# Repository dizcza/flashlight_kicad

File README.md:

# Flashlight PCB design with wooden casing

Kicad PCB design for my wooden flashlight V1 (see https://github.com/dizcza/lasercut_collection). Originally designed by HackLabKyiv residents.

An ordinary 12V LED strip is soldered to the front side of the PCB.

<table>
  <tr>
   <td></td>
   <td></td>
  </tr>
</table>

## Schematics

[schematics.pdf](schematics.pdf)

## Revisions

<table>
  <tr>
   <th>V1</th>
   <th>V2.1</th>
   <th>V2.2</th>
   <th>V3.0</th>
  </tr>
  <tr>
   <td></td>
   <td></td>
   <td></td>
   <td></td>
  </tr>
</table>

## BOM

|Comment             |Designator|Footprint                      |LCSC    |
|--------------------|----------|-------------------------------|--------|
|22uF/25V            |C1,C3,C4  |Capacitor_SMD:C_0805_2012Metric|C45783  |
|1uF                 |C2        |Capacitor_SMD:C_0603_1608Metric|C15849  |
|D_Schottky          |D1,D4,D5  |Diode_SMD:D_SMB                |C22452  |
|USB_B_Micro         |J1        |FlashlightLib:USB-1101IPX6-02  |C2858269|
|10uH                |L1        |FlashlightLib:L_5.0x5.0        |C2849501|
|HSS2333             |Q2        |Package_TO_SOT_SMD:SOT-23      |C15127  |
|1k                  |R1,R2,R3  |Resistor_SMD:R_0603_1608Metric |C21190  |
|10k                 |R4,R6     |Resistor_SMD:R_0603_1608Metric |C25804  |
|200k                |R7        |Resistor_SMD:R_0603_1608Metric |C25811  |
|XB4908A             |U1        |FlashlightLib:XB4908A          |C2998740|
|MT3608              |U2        |Package_TO_SOT_SMD:SOT-23-6    |C84817  |
|TP4057              |U3        |Package_TO_SOT_SMD:TSOT-23-6   |C12044  |
|R6BHC-A05_LED-19-223|U4        |MyFootprints:R6BHC-A05_LED     |C131286 |

## Casing

Can be lasercut or 3d-printed.

DXF file: [casing.dxf](./casing/casing.dxf)

OpenSCAD design file: https://github.com/dizcza/lasercut_collection/blob/master/Lampa.scad

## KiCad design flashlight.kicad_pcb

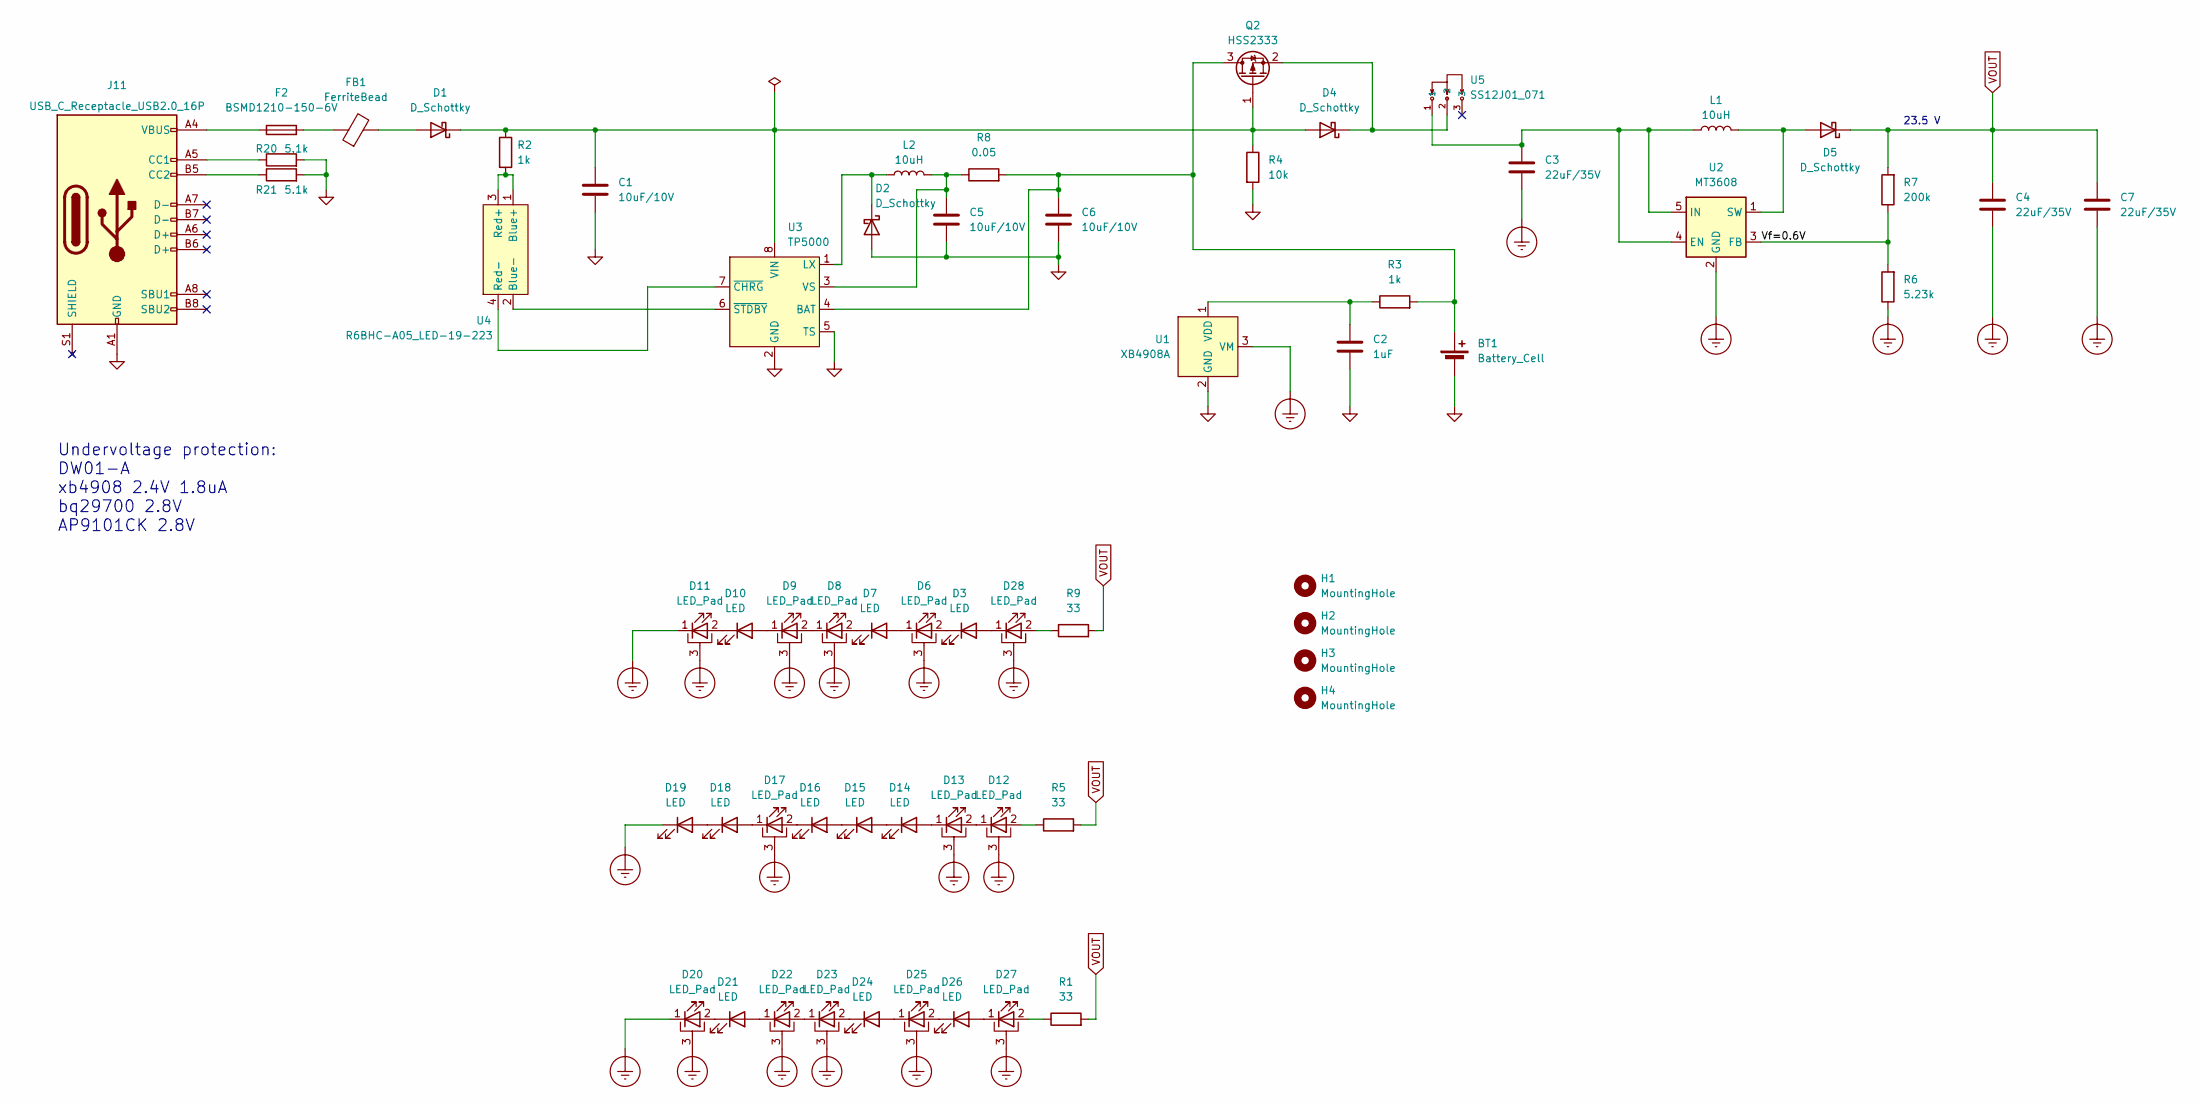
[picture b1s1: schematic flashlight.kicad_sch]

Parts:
BT1: Battery_Cell; BAT-SMD_L82.5.5-W25-BH-21700-B1BJ001; LCSC C20606791
C1, C5, C6: 10uF/10V; C_0603_1608Metric; LCSC C19702
C2: 1uF; C_0603_1608Metric; LCSC C15849
C3, C4, C7: 22uF/35V; C_0805_2012Metric; LCSC C6119901
D1, D2, D4, D5: D_Schottky; D_SMB; LCSC C22452
D3, D7, D10, D14, D15, D16, D18, D19, D21, D24, D26: LED; LED-SMD_L3.0-W1.4-RD_WHITE; LCSC C2843791
D6, D8, D9, D11, D12, D13, D17, D20, D22, D23, D25, D27, D28: LED_Pad; LED-SMD_3P-L5.7-W3.0-RD; LCSC C2843887
F2: BSMD1210-150-6V; Fuse_1210_3225Metric; LCSC C960023
FB1: FerriteBead; L_0805_2012Metric; LCSC C15957
H1, H2, H3, H4: MountingHole; M4-insert
J11: USB_C_Receptacle_USB2.0_16P; USB-SMD_GT-USB-7070A01; LCSC C5446865
L1, L2: 10uH; L_5.0x5.0; LCSC C2849501
Q2: HSS2333; SOT-23; LCSC C15127
R1, R5, R9: 33; R_1206_3216Metric_Pad1.30x1.75mm_HandSolder; LCSC C18005
R2, R3: 1k; R_0603_1608Metric; LCSC C21190
R4: 10k; R_0603_1608Metric; LCSC C25804
R6: 5.23k; R_0805_2012Metric_Pad1.20x1.40mm_HandSolder; LCSC C2933464
R7: 200k; R_0603_1608Metric; LCSC C25811
R8: 0.05; R_1206_3216Metric; LCSC C912768
R20, R21: 5.1k; R_0402_1005Metric; LCSC C25905
U1: XB4908A; ESN-4_L2.8-W2.3-LS3.7-BL; LCSC C2998740
U2: MT3608; SOT23-6-Tight; LCSC C84817
U3: TP5000; ESOP-8_L4.9-W3.9-P1.27-LS6.0-BL-EP; LCSC C5447152
U4: R6BHC-A05_LED-19-223; LED-ARRAY-SMD_4P-L1.6-W1.3-BR-FD; LCSC C131286
U5: SS12J01_071; SW-TH_SHOU-HAN_SS12J01; LCSC C2887258

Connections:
/Vf=0.6V: R6.2, R7.1, U2.3 (FB)
Earth_Protective: C3.2, C4.2, C7.2, D6.3 (PAD), D8.3 (PAD), D9.3 (PAD), D11.1 (K), D11.3 (PAD), D12.3 (PAD), D13.3 (PAD), D17.3 (PAD), D19.1 (K), D20.1 (K), D20.3 (PAD), D22.3 (PAD), D23.3 (PAD), D25.3 (PAD), D27.3 (PAD), D28.3 (PAD), R6.1, U1.3 (VM), U1.4 (VM), U2.2 (GND)
GND: BT1.2 (-), C1.2, C2.2, C5.2, C6.2, D2.2 (A), J11.A1 (GND), J11.A12 (GND), J11.B1 (GND), J11.B12 (GND), R4.2, R20.2, R21.2, U1.2 (GND), U3.2 (GND), U3.5 (TS), U3.9 (GND)
unnamed: BT1.1 (+), C6.1, Q2.3 (D), R3.2, R8.2, U3.4 (BAT)
unnamed: D1.2 (A), FB1.2
unnamed: C1.1, D1.1 (K), D4.2 (A), Q2.1 (G), R2.1, R4.1, U3.8 (VIN)
unnamed: D2.1 (K), L2.1, U3.1 (LX)
unnamed: D3.1 (K), D6.2 (A)
unnamed: D4.1 (K), Q2.2 (S), U5.2
unnamed: D5.2 (A), L1.2, U2.1 (SW)
unnamed: D6.1 (K), D7.2 (A)
unnamed: D7.1 (K), D8.2 (A)
unnamed: D8.1 (K), D9.2 (A)
unnamed: D9.1 (K), D10.2 (A)
unnamed: D10.1 (K), D11.2 (A)
unnamed: D12.2 (A), R5.1
unnamed: D12.1 (K), D13.2 (A)
unnamed: D13.1 (K), D14.2 (A)
unnamed: D14.1 (K), D15.2 (A)
unnamed: D15.1 (K), D16.2 (A)
unnamed: D16.1 (K), D17.2 (A)
unnamed: D17.1 (K), D18.2 (A)
unnamed: D18.1 (K), D19.2 (A)
unnamed: D20.2 (A), D21.1 (K)
unnamed: D21.2 (A), D22.1 (K)
unnamed: D22.2 (A), D23.1 (K)
unnamed: D23.2 (A), D24.1 (K)
unnamed: D24.2 (A), D25.1 (K)
unnamed: D25.2 (A), D26.1 (K)
unnamed: D26.2 (A), D27.1 (K)
unnamed: D27.2 (A), R1.1
unnamed: D28.2 (A), R9.1
unnamed: D3.2 (A), D28.1 (K)
unnamed: F2.1, J11.A4 (VBUS), J11.A9 (VBUS), J11.B4 (VBUS), J11.B9 (VBUS)
unnamed: F2.2, FB1.1
unnamed: J11.A5 (CC1), R20.1
unnamed: J11.B5 (CC2), R21.1
unnamed: C2.1, R3.1, U1.1 (VDD)
unnamed: C3.1, L1.1, U2.4 (EN), U2.5 (IN), U5.1
unnamed: C5.1, L2.2, R8.1, U3.3 (VS)
unnamed: U3.7 (~CHRG), U4.4 (Red-)
unnamed: U3.6 (~STDBY), U4.2 (Blue-)
unnamed: R2.2, U4.1 (Blue+), U4.3 (Red+)
VOUT: C4.1, C7.1, D5.1 (K), R1.2, R5.2, R7.2, R9.2

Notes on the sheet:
23.5 V
Undervoltage protection: DW01-A xb4908 2.4V 1.8uA bq29700 2.8V AP9101CK 2.8V

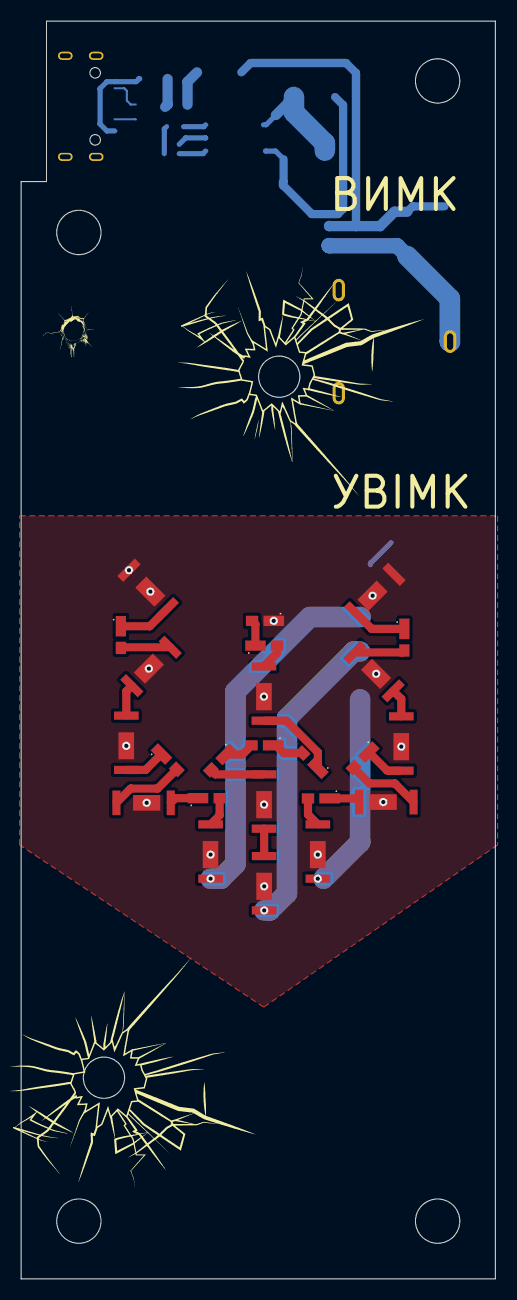
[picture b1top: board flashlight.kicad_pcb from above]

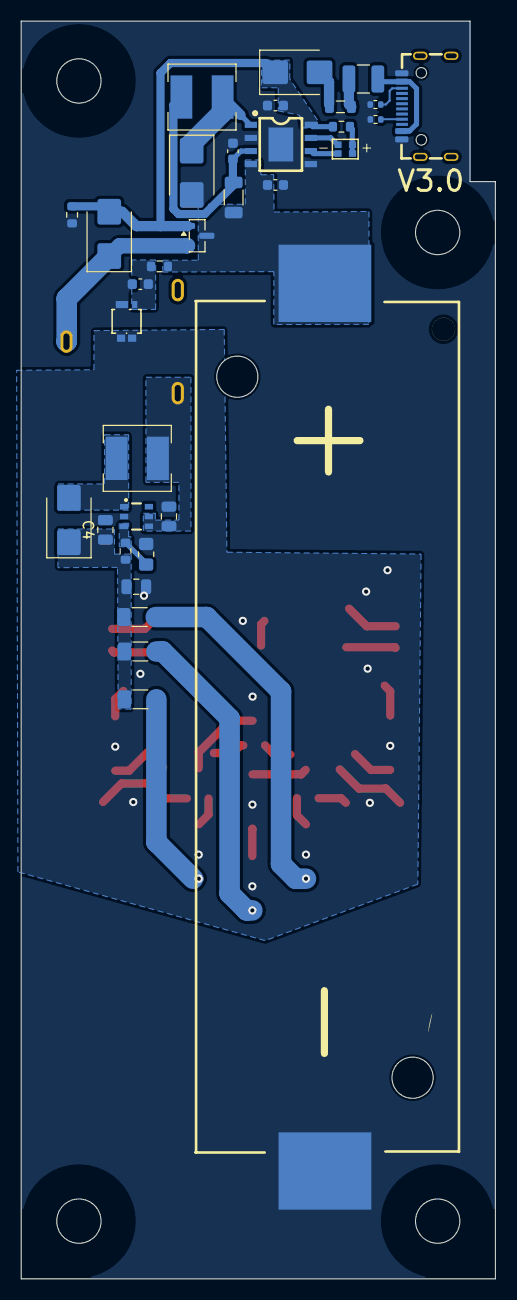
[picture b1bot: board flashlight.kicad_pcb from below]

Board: 2 copper layers, 46.0 x 122.0 mm, 62 parts (33 on the bottom side), 44 nets.

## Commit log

2023-12-07 v0.1
2023-12-07 v0.2
2023-12-07 v0.3
2023-12-07 v0.4_work
2023-12-08 jlcpcb completed
2023-12-08 18.24 Volts 4.70
2023-12-08 led strip
2023-12-09 JLCPCB ordered
2024-01-22 shortened GND paths
2024-01-22 added schematics
2024-01-22 casing info
2024-01-23 upd v2.2
2024-01-23 casing svg
2024-01-23 0603 footprint
2024-01-25 v2.2.1
2024-01-25 copper pour
2024-01-26 v2.2.2
2024-01-28 tight sot23-6
2024-01-28 v2.3
2024-06-21 v2.4: double led
2024-07-21 v2.4 xb4908A undervoltage protection
2024-08-10 increased 18650 pads size, added led stripe silkscreen line, increased switch hole length by 0.1mm
2024-08-15 undervoltage protection only
2024-08-15 xb4908 v2.5
2024-09-14 moved TP4057 closer to the VBAT
2024-09-14 v2.6: board outline 4mm
2024-11-11 v2.7 boxes
2025-10-27 V3.0 21700 3x8 leds
2025-10-27 bullet hole images
2025-10-28 fixed C4 cap issue
2025-10-29 Added an extra out capacitor
